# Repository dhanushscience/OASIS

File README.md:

# PROJECT OASIS

### Launching soon.

A context-aware control surface for developers.

It watches the app in focus, suggests AI mappings, and runs automations so every key does the right thing for the moment.

Built in **149 hours.**

---

## See it

**[dhanushscience.github.io/OASIS](https://dhanushscience.github.io/PROJECT-OASIS/)**

Scroll the workbench. Watch it assemble. Feel what is coming.

---

## Get first access

Star this repo to show interest.

When OASIS launches, people who starred get first access.

**[★ Star OASIS](https://github.com/dhanushscience/PROJECT-OASIS)**

Open source if the response is there.

---

<p align="center">
  <sub>Designed by <a href="https://www.linkedin.com/in/dhanushscience">Dhanush Science</a></sub>
</p>

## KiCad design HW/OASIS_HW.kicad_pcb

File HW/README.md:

# OASIS Hardware

Custom macro-pad PCB built around the **Seeed XIAO ESP32-C3** module.

## Project files

| File | Purpose |
|------|---------|
| `OASIS_HW.kicad_pro` | KiCad 10 project |
| `OASIS_HW.kicad_sch` | Schematic |
| `OASIS_HW.kicad_pcb` | PCB layout (2-layer, 1.6 mm) |
| `GERBER.zip` | Manufacturing export (Gerber + drill) |

Open the project in [KiCad 10](https://www.kicad.org/) or newer.

## Key components

| Ref | Part | Role |
|-----|------|------|
| XIAO | Seeed XIAO-ESP32-C3-SMD | MCU, BLE radio |
| TOE, TAC, TIC | APEM Multimec MEC tactile switches | Three macro buttons |
| OLED | 0.49″ display module | **Not fitted in this version** (see note below) |
| TYPE-C | TYPE-C-31-G-10 | USB-C power |
| BATTERY | 2-pin connector | Optional battery input |
| PWR_SW | Power switch | Main power control |

Supporting passives (pull-ups, dividers) are on the schematic.

## Manufacturing

Unzip **`GERBER.zip`** and use:

- Copper: `OASIS_HW-F_Cu.gbr`, `OASIS_HW-B_Cu.gbr`
- Masks / paste / silkscreen: `F_*` and `B_*` layers
- Drills: `OASIS_HW-PTH.drl`, `OASIS_HW-NPTH.drl`
- Job file: `OASIS_HW-job.gbrjob`

Standard stack: **2-layer FR4, 1.6 mm**.

## Resource folder

`Resource/` holds vendor footprints, symbols, and 3D models used by the design (XIAO ESP32-C3 reference, USB-C connector, switch footprints, etc.). Only the parts this board uses are kept.

## OLED not fitted

The OLED is deliberately left off this version to save battery and extend the device's runtime. The firmware runs headless with display stubs (`OASIS_HAS_DISPLAY=0`), and status is shown in the app instead. The I2C pins (GPIO6/7) are reserved for a future display.

## MCU pin map (firmware)

| GPIO | Net | Function |
|------|-----|----------|
| 3 | TIC | Button 0 (SW1) |
| 4 | TAC | Button 1 (SW2) |
| 5 | TOE | Button 2 (SW3) |
| 6 | SDA | OLED I2C (reserved, not fitted) |
| 7 | SCL | OLED I2C (reserved, not fitted) |
| 2 | B_LVL | Battery ADC (220k/220k divider) |

## After fab

1. Solder the XIAO ESP32-C3 and passives per the schematic.
2. Flash firmware from [`FW/`](../FW/) (`pio run -t upload`, ESP-IDF).
3. Pair with the OasisShell Windows app ([`../SW/`](../SW/)).

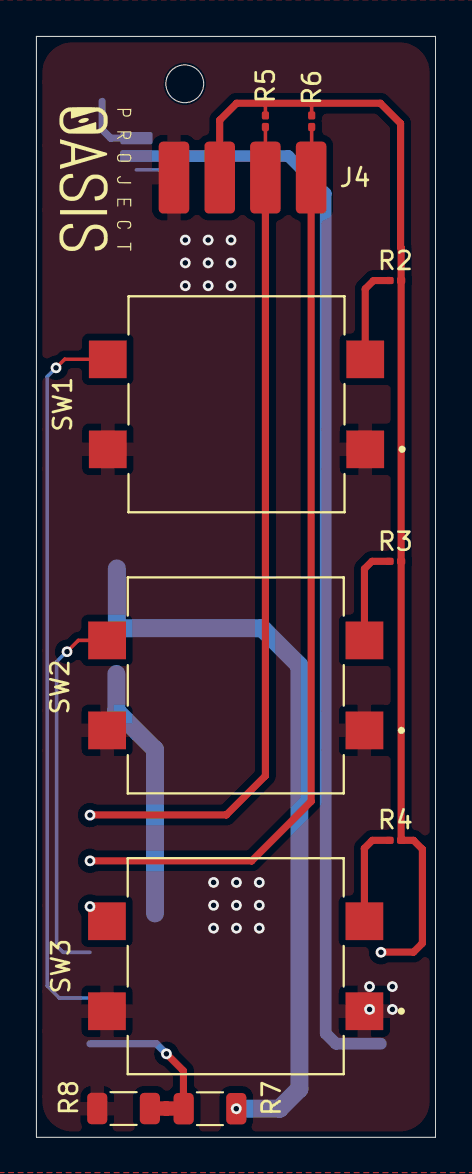
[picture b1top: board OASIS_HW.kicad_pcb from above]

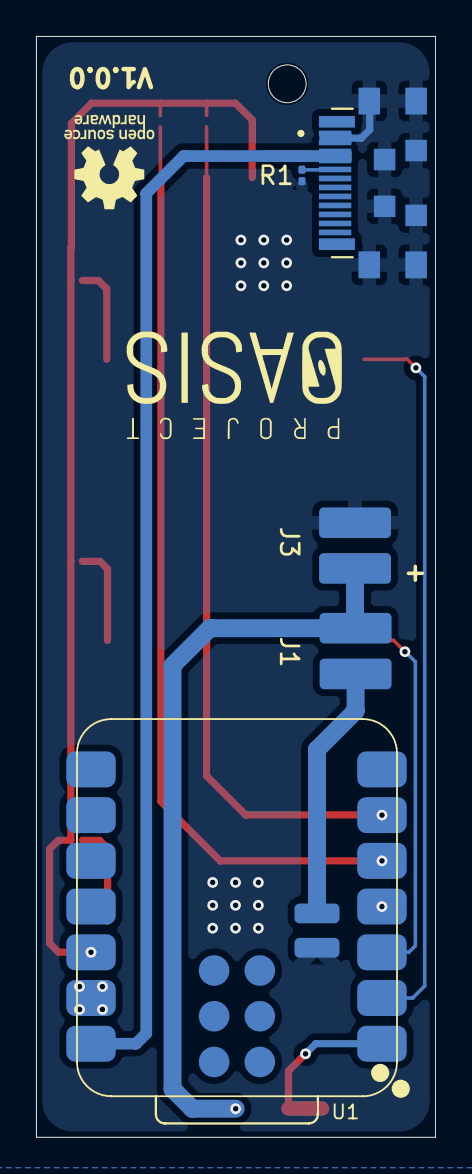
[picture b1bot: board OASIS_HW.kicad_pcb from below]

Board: 2 copper layers, 22.2 x 61.2 mm, 16 parts (5 on the bottom side), 12 nets.

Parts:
J1: BATTERY; PinHeader_1x02_P2.54mm_Vertical
J2: TYPE-C-31-G-10; HRO_TYPE-C-31-G-10
J3: PWR_SW; PinHeader_1x02_P2.54mm_Vertical
J4: OLED; PinSocket_1x04_P2.54mm_Vertical
R1: 5.1k; R_0201_0603Metric
R2, R3, R4: 10k; R_0201_0603Metric
R5, R6: 4.7k; R_0201_0603Metric
R7, R8: 220k; R_1206_3216Metric
SW1: TIC; SW_TS16-1212-75-BK-100-SMT-TR
SW2: TAC; SW_TS16-1212-75-BK-100-SMT-TR
SW3: TOE; SW_TS16-1212-75-BK-100-SMT-TR
U1: XIAO-ESP32-C3-SMD

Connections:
+3.3V: J4.3, R2.1, R3.1, R4.1, R5.1, R6.1, U1.12 (3V3)
+5V: J2.A4 (VBUS_A), J2.B9 (VBUS_B), U1.14 (VBUS)
BAT: J3.2, U1.21
B_LVL: R7.1, R8.1, U1.1 (GPIO2_A0_D0)
GND: J1.2, J2.A1 (GND_A), J2.B12 (GND_B), J2.SH1 (SHIELD), J2.SH2 (SHIELD), J2.SH3 (SHIELD), J2.SH4 (SHIELD), J2.SH5 (SHIELD), J2.SH6 (SHIELD), J2.SH7 (SHIELD), J2.SH8 (SHIELD), J4.4, R1.2, R8.2, SW1.1 (A), SW1.2 (A), SW2.1 (A), SW2.2 (A), SW3.1 (A), SW3.2 (A), U1.13 (GND), U1.22
unnamed: J1.1, J3.1, R7.2
unnamed: J2.A5 (CC), R1.1
SCL: J4.2, R5.2, U1.6 (GPIO7_D5_SCL)
SDA: J4.1, R6.2, U1.5 (GPIO6_D4_SDA)
TAC: R3.2, SW2.3 (B), U1.3 (GPIO4_A2_D2)
TIC: R2.2, SW1.3 (B), U1.2 (GPIO3_A1_D1)
TOE: R4.2, SW3.3 (B), U1.4 (GPIO5_A3_D3)
